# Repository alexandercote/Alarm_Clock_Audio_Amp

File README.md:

# Alarm_Clock
Design class project where I worked in a group of 3 to implement a music playing alarm clock using a microcontroller board.
Features included displaying time on a 7 segment display, alarm buttons, snooze, ability to change time
and volume control. 

Each subfolder has README's describing the logic behind the decision and pictures demonstrating the contents of the files.

Alarm clock functionality:
- Change the displayed time, date, and alarm time.
- LED's indicate what mode you are currently in. 
     Modes include: Time/Date/Alarm Set, Snooze, and Default.
- Display time in both 12 hour(with AM/PM indicator) and 24 hour 
  formats.
- Choose from different songs placed on the internal storage (a 
  USB drive for our purposes)
- Change the volume of the song using a knob in the center.
- Snooze the alarm both with a push button on the case, and with your 
  phone over bluetooth.
- Use of external power supply (9V battery) for louder audio output.
- Ability to disable the alarm entirely and use it as a clock.

Demonstration of the alarm clock can be found in the following video:
https://www.youtube.com/watch?v=fe28Ro4kcdw

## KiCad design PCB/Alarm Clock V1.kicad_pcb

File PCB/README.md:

# The Circuit

###### Design Limitation:
  - Have the following capacitors: 1nF, 10uF, 470uF and 100 nF
  - Resistors: 5% Resistors.
  - Input Voltage for audio input: [0-3V], DC voltage = 1.5V, with AC voltage = ± 0.3V. 
  - The audio input has source impedance of 20kΩ and has a maximum current source of 25mA.
  - From the data sheet, the impedance of the speaker is 8Ω.

Schematic view of the top hierarchy view, including push button debouncing, with an audio amplifier and LED multiplexer in lower hierarchy schematics.

###### Audio Amplifier:
  - Cascaded Low-Pass and High-Pass Filter to create a BandPass Filter with a pass band of 19.85Hz to 19.4kHz
  - Using the LM386 without its gain pins connected will result in a voltage gain of 20. Since (20 * 0.5V) = 10V, which is higher than 
    our source voltage, we need to voltage divide the input of LM386. (0.5V is the maximum input AC swing). Here, we chose a maximum 
    voltage of 4.5V to make sure the gain stays linear. From that, we found our values for resistors in the voltage divider. A 100kΩ
    potientiometer was used to dynamically set the gain (and therefore the volume)The potentiometer will always show 100 kΩ to the 
    High-Pass Filter, with the LM386 only seeing the resistance set in order to set the volume.

Schematic view of the audio amplifier schematic. Includes a low pass filter cascaded with a high-pass filter, a potentiometer for input voltage control, and an LM386 to amplify.

The schematic view of the LED multiplexing circuit:

The PCB (Two layer):

Top layer PCB view:

Top layer view from the manufacturer (OshPark):

Bottom layer PCB view:

Bottom layer view from the manufacturer:

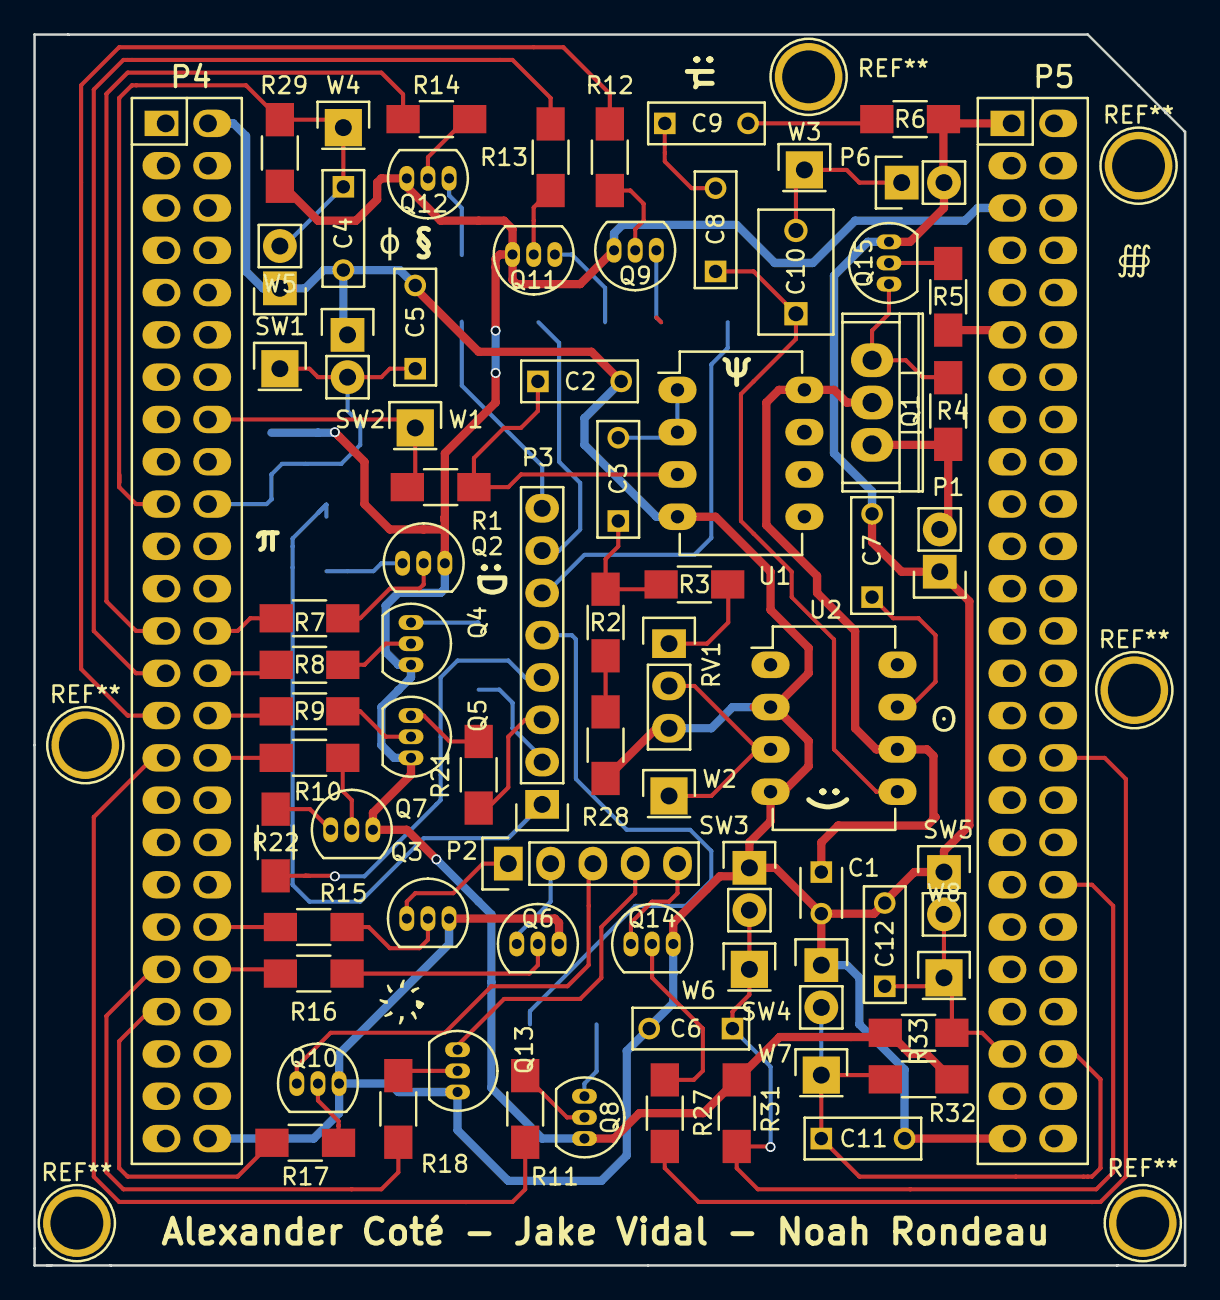
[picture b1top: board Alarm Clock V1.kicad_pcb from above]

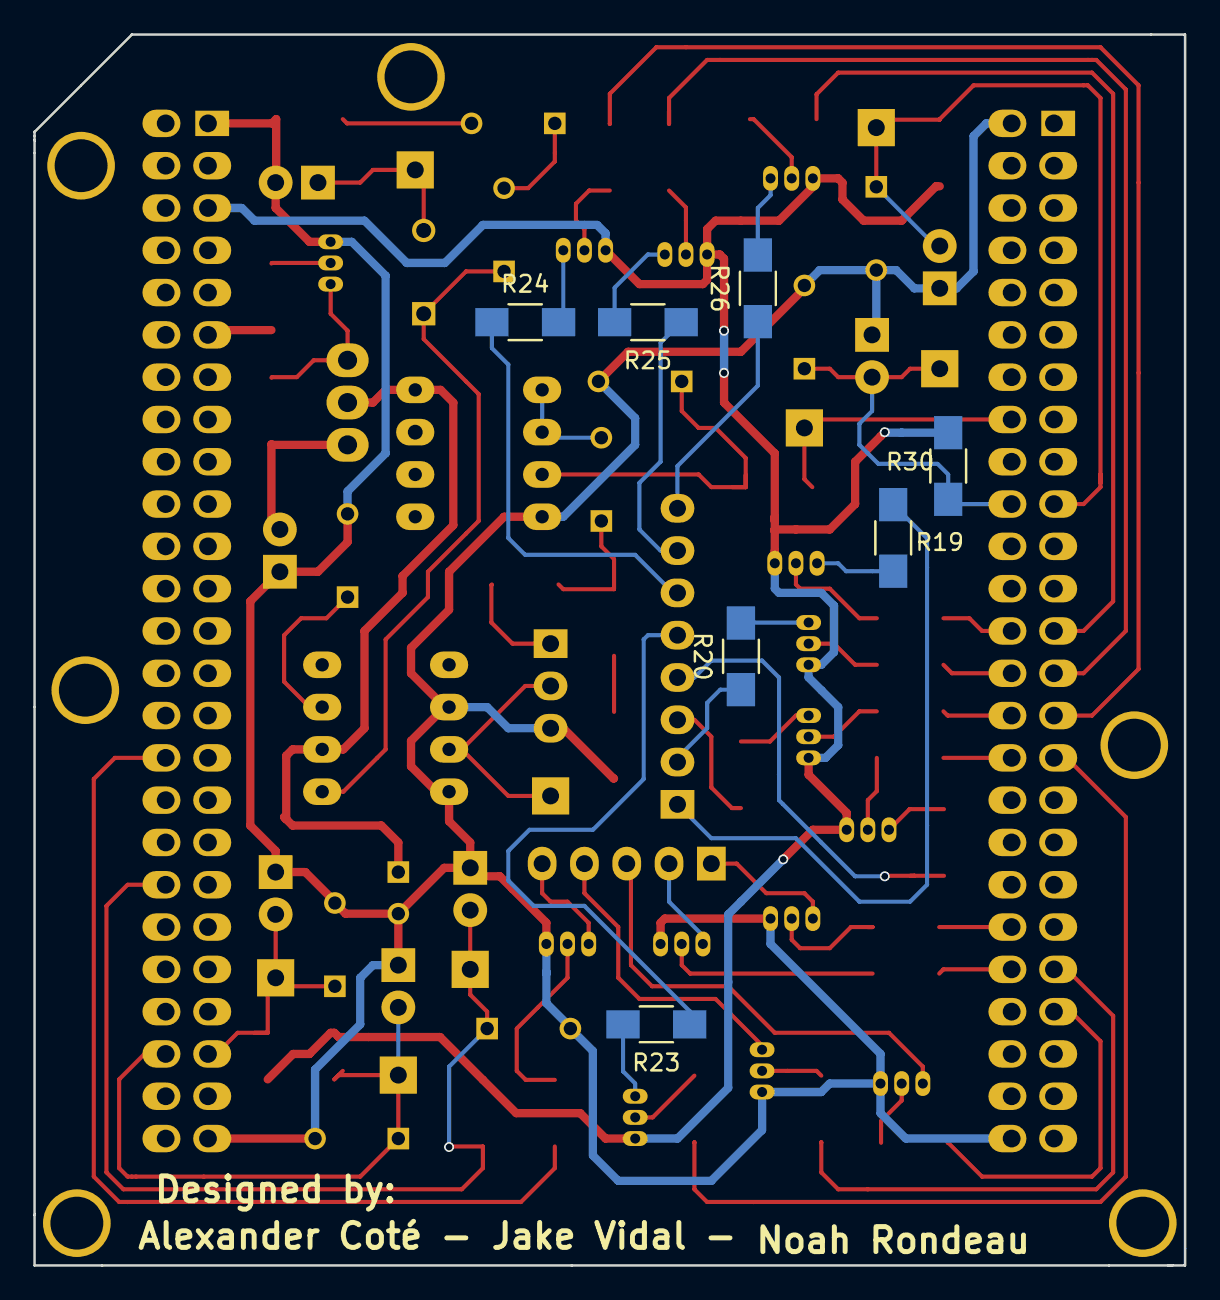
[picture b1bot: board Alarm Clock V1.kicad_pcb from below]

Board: 2 copper layers, 69.1 x 73.9 mm, 82 parts (7 on the bottom side), 71 nets.

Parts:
C1: 10 uF; C_Disc_D3_P2.5
C2, C3, C4, C5, C6, C7, C8, C9, C11, C12: 100 nF; C_Rect_L7_W2.5_P5
C10: 470 uF; C_Disc_D7.5_P5
P1, P6: CONN_01X02; Pin_Header_Straight_1x02
P2: CONN_01X05; Pin_Header_Straight_1x05
P3: CONN_01X08; Pin_Header_Straight_1x08
P4, P5: STM32_F4_ConnV2
Q1: IRLIB9343; TO-220
Q2, Q4, Q5, Q7, Q8, Q9, Q11, Q12: 2N3906; TO-92_Inline_Narrow_Oval
Q3, Q6, Q10, Q13, Q14, Q15: 2N3904; TO-92_Inline_Narrow_Oval
R1: 82 Ω; R_1206_HandSoldering
R2, R3: 120 kΩ; R_1206_HandSoldering
R4: 100 kΩ; R_1206_HandSoldering
R5, R7, R8, R9, R10, R11, R12, R13, R14, R15, R16, R17, R18, R27: 1 kΩ; R_1206_HandSoldering
R6: 10 Ω; R_1206_HandSoldering
R19, R20, R21, R22, R23, R24, R25, R26: 100 Ω; R_1206_HandSoldering
R28: 6.2 kΩ; R_1206_HandSoldering
R29, R30, R31, R32, R33: 47 kΩ; R_1206_HandSoldering
RV1: POT: 100 kΩ; Pin_Header_Straight_1x03
SW1, SW2, SW3, SW4, SW5: SW_PUSH; Pin_Header_Straight_1x02
U1: LM358N; DIP-8_W7.62mm_LongPads
U2: LM386; DIP-8_W7.62mm_LongPads
W1, W2, W3, W4, W5, W6, W7, W8: TEST_1P; Pin_Header_Straight_1x01

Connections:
/AlarmClockAmplifier/3.3V: P5.11, R5.2
/AlarmClockAmplifier/9V: P1.2, Q1.3, R4.2
/AlarmClockAmplifier/GND: C1.2, C2.2, C4.2, C5.2, C6.2, C7.2, C11.2, C12.2, P1.1, P4.2, P4.50, P5.1, P5.49, P6.2, Q3.3, Q6.3, Q10.3, Q13.3, Q14.3, Q15.3, R6.2, R28.2, RV1.3, SW1.1, SW2.1, SW3.1, SW4.1, SW5.1, U1.4, U2.2, U2.4
/AlarmClockAmplifier/Output: C10.2, P6.1, W3.1
/AlarmClockAmplifier/Signal: P4.16, R1.2, W1.1
/LEDSelect/1: P4.40, R15.2
/LEDSelect/2: P4.42, R16.2
/LEDSelect/3: P4.43, R17.2
/LEDSelect/3V: P5.5, Q2.3, Q4.3, Q5.3, Q7.3, Q8.3, Q9.3, Q11.3, Q12.3, R29.1, R30.1, R31.1, R32.1, R33.1
/LEDSelect/4: P4.41, R18.2
/LEDSelect/5: P5.32, R27.2
/LEDSelect/Digit_1: P2.1, Q3.1
/LEDSelect/Digit_2: P2.2, Q6.1
/LEDSelect/Digit_3: P2.4, Q13.1
/LEDSelect/Digit_4: P2.5, Q14.1
/LEDSelect/P3: P3.4, R22.1
/LEDSelect/P4: P2.3, Q10.1
/LEDSelect/P5: P3.5, R23.1
/LEDSelect/P7: P3.8, R26.1
/LEDSelect/P11: P3.6, R24.1
/LEDSelect/P13: P3.3, R21.1
/LEDSelect/P14: P3.1, R19.1
/LEDSelect/P15: P3.7, R25.1
/LEDSelect/P16: P3.2, R20.1
/LEDSelect/a: P4.26, R7.2
/LEDSelect/b: P4.28, R8.2
/LEDSelect/c: P4.30, R9.2
/LEDSelect/d: P4.32, R10.2
/LEDSelect/e: P4.31, R11.2
/LEDSelect/f: P4.29, R12.2
/LEDSelect/g: P4.27, R13.2
/LEDSelect/h: P4.25, R14.2
/PC4: C5.1, P4.20, R30.2, SW2.2, W5.1
/PC5: C4.1, P4.19, R29.2, SW1.2, W4.1
/PC8: C12.1, P5.45, R33.2, SW5.2, W8.1
/PC9: C11.1, P5.46, R32.2, SW4.2, W7.1
/PC11: C6.1, P5.38, R31.2, SW3.2, W6.1
unnamed: C1.1, Q1.2, U1.8, U2.6
unnamed: C2.1, R1.1, U1.3
unnamed: C3.1, R2.1, R3.1
unnamed: C3.2, U1.1, U1.2
unnamed: C7.1, U2.7
unnamed: C8.2, C9.1
unnamed: C9.2, R6.1
unnamed: C8.1, C10.1, U2.5
unnamed: Q1.1, Q15.1, R4.1
unnamed: Q2.1, R19.2
unnamed: Q2.2, R7.1
unnamed: Q3.2, R15.1
unnamed: Q4.1, R20.2
unnamed: Q4.2, R8.1
unnamed: Q5.1, R21.2
unnamed: Q5.2, R9.1
unnamed: Q6.2, R16.1
unnamed: Q7.1, R22.2
unnamed: Q7.2, R10.1
unnamed: Q8.1, R23.2
unnamed: Q8.2, R11.1
unnamed: Q9.1, R24.2
unnamed: Q9.2, R12.1
unnamed: Q10.2, R17.1
unnamed: Q11.1, R25.2
unnamed: Q11.2, R13.1
unnamed: Q12.1, R26.2
unnamed: Q12.2, R14.1
unnamed: Q13.2, R18.1
unnamed: Q14.2, R27.1
unnamed: Q15.2, R5.1
unnamed: R2.2, R28.1
unnamed: R3.2, RV1.1
unnamed: RV1.2, U2.3, W2.1

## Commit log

2017-05-01 Added SolidWorks case files and pdf description
2017-05-01 Added PCB Files
2017-05-03 Rename PCB.md to README.md
2017-06-05 Updated PCB - Final version that was sent to fab
